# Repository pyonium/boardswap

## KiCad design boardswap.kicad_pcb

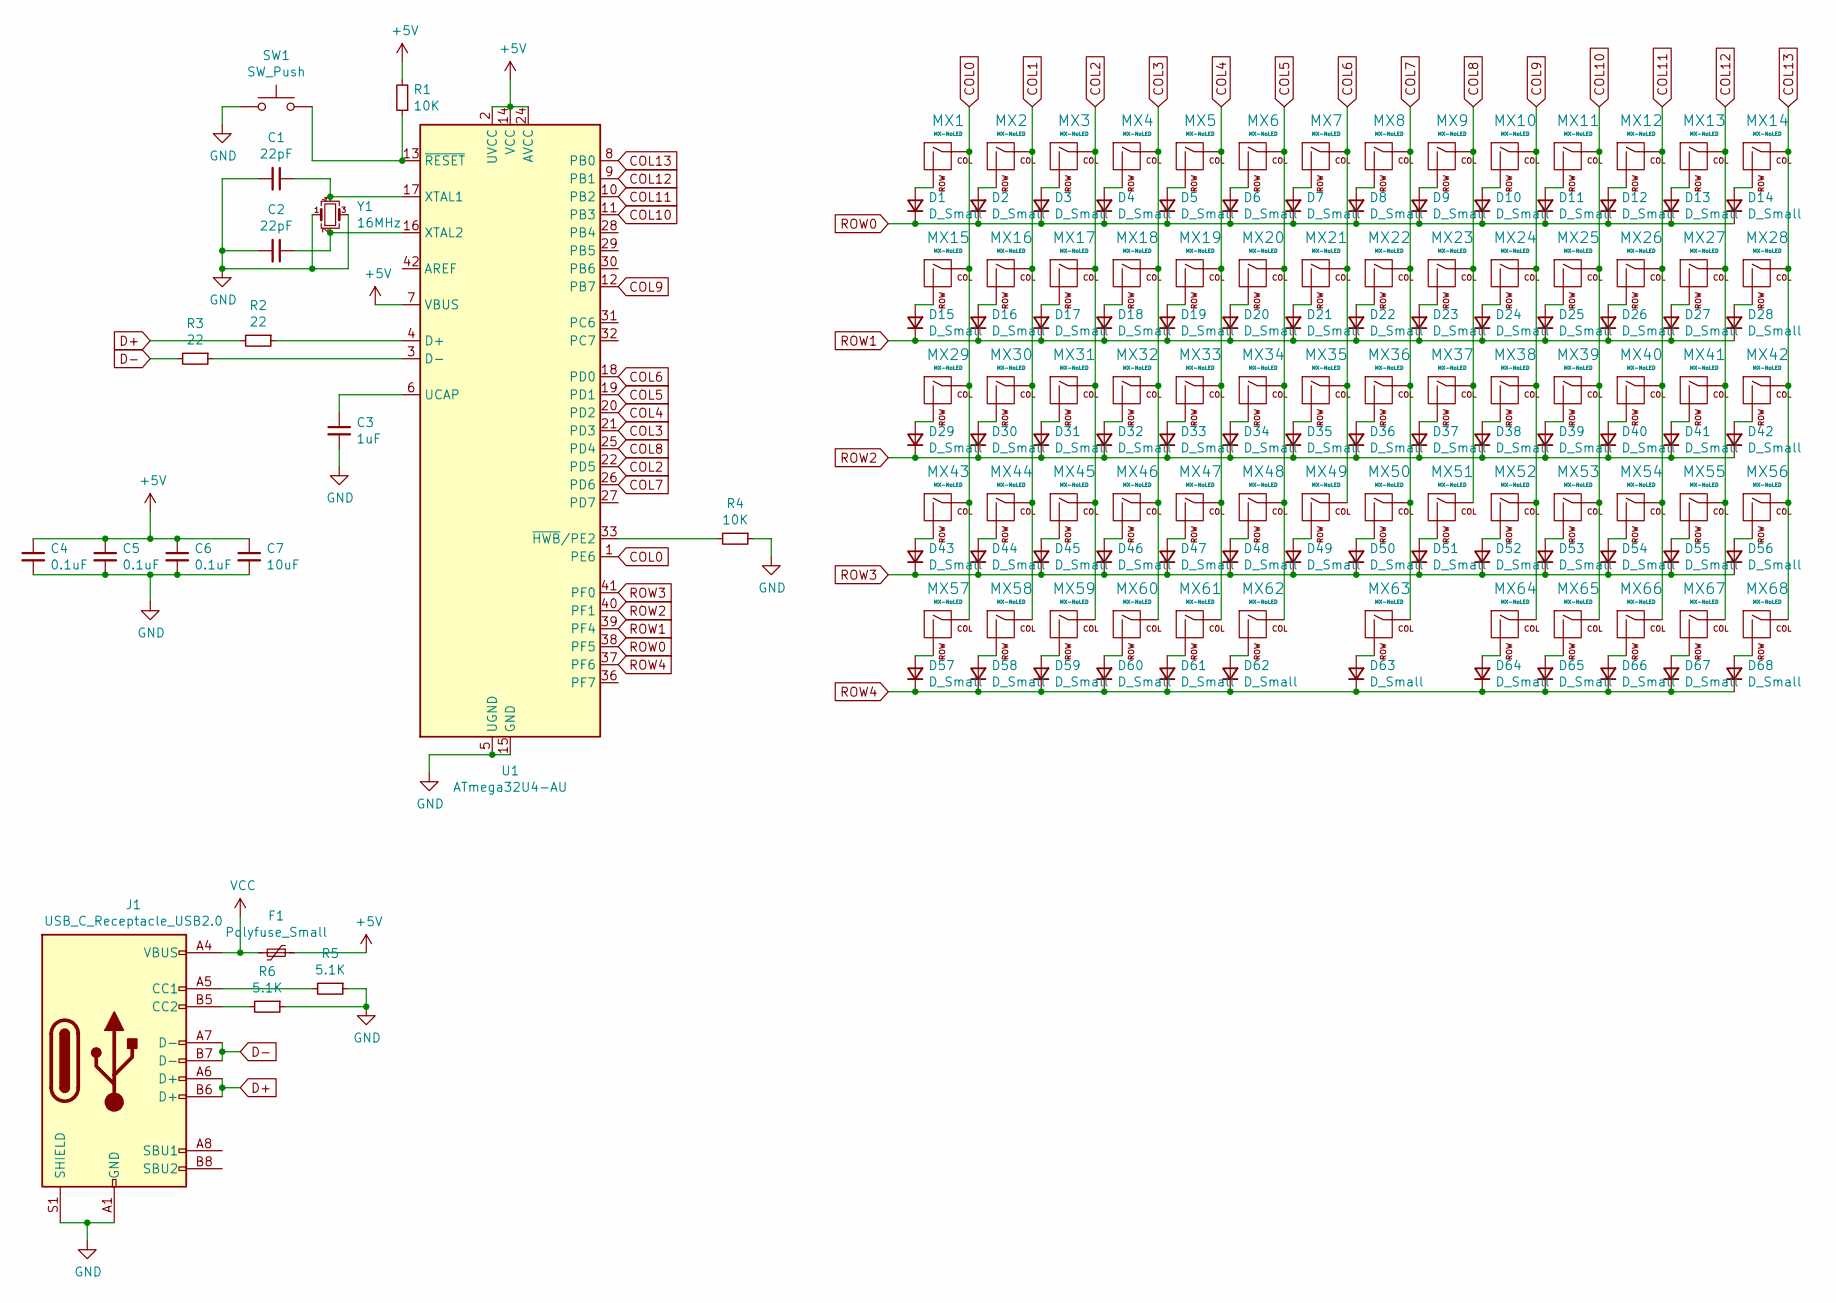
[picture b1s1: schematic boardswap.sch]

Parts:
C1, C2: 22pF; C_0805_2012Metric; LCSC C1804
C3: 1uF; C_0805_2012Metric; LCSC C282736
C4, C5, C6: 0.1uF; C_0603_1608Metric; LCSC C14663
C7: 10uF; C_0603_1608Metric; LCSC C344022
D1, D2, D3, D4, D5, D6, D7, D8, D9, D10, D11, D12, D13, D14, D15, D16, D17, D18, D19, D20, D21, D22, D23, D24, D25, D26, D27, D28, D29, D30, D31, D32, D33, D34, D35, D36, D37, D38, D39, D40, D41, D42, D43, D44, D45, D46, D47, D48, D49, D50, D51, D52, D53, D54, D55, D56, D57, D58, D59, D60, D61, D62, D63, D64, D65, D66, D67, D68: D_Small; D_SOD-123; LCSC C64885
F1: Polyfuse_Small; Fuse_1206_3216Metric; LCSC C70068
J1: USB_C_Receptacle_USB2.0; USB_C_Receptacle_HRO_TYPE-C-31-M-12
MX1, MX2, MX3, MX4, MX5, MX6, MX7, MX8, MX9, MX10, MX11, MX12, MX13, MX14, MX15, MX16, MX17, MX18, MX19, MX20, MX21, MX22, MX23, MX24, MX25, MX26, MX27, MX28, MX29, MX30, MX31, MX32, MX33, MX34, MX35, MX36, MX37, MX38, MX39, MX40, MX41, MX42, MX43, MX44, MX45, MX46, MX47, MX48, MX49, MX50, MX51, MX52, MX53, MX54, MX55, MX56, MX57, MX58, MX59, MX60, MX61, MX62, MX63, MX64, MX65, MX66, MX67, MX68: MX-NoLED; Kailh_socket_MX_alt
R1, R4: 10K; R_0805_2012Metric; LCSC C55866
R2, R3: 22; R_0805_2012Metric; LCSC C17561
R5, R6: 5.1K; R_0805_2012Metric; LCSC C64462
SW1: SW_Push; SW_SPST_SKQG_WithStem
U1: ATmega32U4-AU; TQFP-44_10x10mm_P0.8mm; LCSC C44854
Y1: 16MHz; Crystal_SMD_3225-4Pin_3.2x2.5mm; LCSC C13738

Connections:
+5V: C4.1, C5.1, C6.1, C7.1, F1.1, R1.2, U1.2 (UVCC), U1.7 (VBUS), U1.14 (VCC), U1.24 (AVCC), U1.34 (VCC), U1.44 (AVCC)
COL0: MX1.1 (COL), MX15.1 (COL), MX29.1 (COL), MX43.1 (COL), MX57.1 (COL), U1.1 (PE6)
COL1: MX2.1 (COL), MX16.1 (COL), MX30.1 (COL), MX44.1 (COL), MX58.1 (COL)
COL2: MX3.1 (COL), MX17.1 (COL), MX31.1 (COL), MX45.1 (COL), MX59.1 (COL), U1.22 (PD5)
COL3: MX4.1 (COL), MX18.1 (COL), MX32.1 (COL), MX46.1 (COL), MX60.1 (COL), U1.21 (PD3)
COL4: MX5.1 (COL), MX19.1 (COL), MX33.1 (COL), MX47.1 (COL), MX61.1 (COL), U1.20 (PD2)
COL5: MX6.1 (COL), MX20.1 (COL), MX34.1 (COL), MX48.1 (COL), MX62.1 (COL), U1.19 (PD1)
COL6: MX7.1 (COL), MX21.1 (COL), MX35.1 (COL), MX49.1 (COL), U1.18 (PD0)
COL7: MX8.1 (COL), MX22.1 (COL), MX36.1 (COL), MX50.1 (COL), MX63.1 (COL), U1.26 (PD6)
COL8: MX9.1 (COL), MX23.1 (COL), MX37.1 (COL), MX51.1 (COL), U1.25 (PD4)
COL9: MX10.1 (COL), MX24.1 (COL), MX38.1 (COL), MX52.1 (COL), MX64.1 (COL), U1.12 (PB7)
COL10: MX11.1 (COL), MX25.1 (COL), MX39.1 (COL), MX53.1 (COL), MX65.1 (COL), U1.11 (PB3)
COL11: MX12.1 (COL), MX26.1 (COL), MX40.1 (COL), MX54.1 (COL), MX66.1 (COL), U1.10 (PB2)
COL12: MX13.1 (COL), MX27.1 (COL), MX41.1 (COL), MX55.1 (COL), MX67.1 (COL), U1.9 (PB1)
COL13: MX14.1 (COL), MX28.1 (COL), MX42.1 (COL), MX56.1 (COL), MX68.1 (COL), U1.8 (PB0)
D+: J1.A6 (D+), J1.B6 (D+), R2.2
D-: J1.A7 (D-), J1.B7 (D-), R3.2
GND: C1.2, C2.2, C3.2, C4.2, C5.2, C6.2, C7.2, J1.A1 (GND), J1.A12 (GND), J1.B1 (GND), J1.B12 (GND), J1.S1 (SHIELD), R4.1, R5.1, R6.1, SW1.1, U1.5 (UGND), U1.15 (GND), U1.23 (GND), U1.35 (GND), U1.43 (GND), Y1.1, Y1.3
unnamed: C1.1, U1.17 (XTAL1), Y1.4
unnamed: C2.1, U1.16 (XTAL2), Y1.2
unnamed: C3.1, U1.6 (UCAP)
unnamed: D1.2 (A), MX1.2 (ROW)
unnamed: D2.2 (A), MX2.2 (ROW)
unnamed: D3.2 (A), MX3.2 (ROW)
unnamed: D4.2 (A), MX4.2 (ROW)
unnamed: D5.2 (A), MX5.2 (ROW)
unnamed: D6.2 (A), MX6.2 (ROW)
unnamed: D7.2 (A), MX7.2 (ROW)
unnamed: D8.2 (A), MX8.2 (ROW)
unnamed: D9.2 (A), MX9.2 (ROW)
unnamed: D10.2 (A), MX10.2 (ROW)
unnamed: D11.2 (A), MX11.2 (ROW)
unnamed: D12.2 (A), MX12.2 (ROW)
unnamed: D13.2 (A), MX13.2 (ROW)
unnamed: D14.2 (A), MX14.2 (ROW)
unnamed: D15.2 (A), MX15.2 (ROW)
unnamed: D16.2 (A), MX16.2 (ROW)
unnamed: D17.2 (A), MX17.2 (ROW)
unnamed: D18.2 (A), MX18.2 (ROW)
unnamed: D19.2 (A), MX19.2 (ROW)
unnamed: D20.2 (A), MX20.2 (ROW)
unnamed: D21.2 (A), MX21.2 (ROW)
unnamed: D22.2 (A), MX22.2 (ROW)
unnamed: D23.2 (A), MX23.2 (ROW)
unnamed: D24.2 (A), MX24.2 (ROW)
unnamed: D25.2 (A), MX25.2 (ROW)
unnamed: D26.2 (A), MX26.2 (ROW)
unnamed: D27.2 (A), MX27.2 (ROW)
unnamed: D28.2 (A), MX28.2 (ROW)
unnamed: D29.2 (A), MX29.2 (ROW)
unnamed: D30.2 (A), MX30.2 (ROW)
unnamed: D31.2 (A), MX31.2 (ROW)
unnamed: D32.2 (A), MX32.2 (ROW)
unnamed: D33.2 (A), MX33.2 (ROW)
unnamed: D34.2 (A), MX34.2 (ROW)
unnamed: D35.2 (A), MX35.2 (ROW)
unnamed: D36.2 (A), MX36.2 (ROW)
unnamed: D37.2 (A), MX37.2 (ROW)
unnamed: D38.2 (A), MX38.2 (ROW)
unnamed: D39.2 (A), MX39.2 (ROW)
unnamed: D40.2 (A), MX40.2 (ROW)
unnamed: D41.2 (A), MX41.2 (ROW)
unnamed: D42.2 (A), MX42.2 (ROW)
unnamed: D43.2 (A), MX43.2 (ROW)
unnamed: D44.2 (A), MX44.2 (ROW)
unnamed: D45.2 (A), MX45.2 (ROW)
unnamed: D46.2 (A), MX46.2 (ROW)
unnamed: D47.2 (A), MX47.2 (ROW)
unnamed: D48.2 (A), MX48.2 (ROW)
unnamed: D49.2 (A), MX49.2 (ROW)
unnamed: D50.2 (A), MX50.2 (ROW)
unnamed: D51.2 (A), MX51.2 (ROW)
unnamed: D52.2 (A), MX52.2 (ROW)
unnamed: D53.2 (A), MX53.2 (ROW)
unnamed: D54.2 (A), MX54.2 (ROW)
unnamed: D55.2 (A), MX55.2 (ROW)
unnamed: D56.2 (A), MX56.2 (ROW)
unnamed: D57.2 (A), MX57.2 (ROW)
unnamed: D58.2 (A), MX58.2 (ROW)
unnamed: D59.2 (A), MX59.2 (ROW)
unnamed: D60.2 (A), MX60.2 (ROW)
unnamed: D61.2 (A), MX61.2 (ROW)
unnamed: D62.2 (A), MX62.2 (ROW)
unnamed: D63.2 (A), MX63.2 (ROW)
unnamed: D64.2 (A), MX64.2 (ROW)
unnamed: D65.2 (A), MX65.2 (ROW)
unnamed: D66.2 (A), MX66.2 (ROW)
unnamed: D67.2 (A), MX67.2 (ROW)
unnamed: D68.2 (A), MX68.2 (ROW)
unnamed: J1.A5 (CC1), R5.2
unnamed: J1.B5 (CC2), R6.2
unnamed: R1.1, SW1.2, U1.13 (~RESET)
unnamed: R2.1, U1.4 (D+)
unnamed: R3.1, U1.3 (D-)
unnamed: R4.2, U1.33 (~HWB~/PE2)
ROW0: D1.1 (K), D2.1 (K), D3.1 (K), D4.1 (K), D5.1 (K), D6.1 (K), D7.1 (K), D8.1 (K), D9.1 (K), D10.1 (K), D11.1 (K), D12.1 (K), D13.1 (K), D14.1 (K), U1.38 (PF5)
ROW1: D15.1 (K), D16.1 (K), D17.1 (K), D18.1 (K), D19.1 (K), D20.1 (K), D21.1 (K), D22.1 (K), D23.1 (K), D24.1 (K), D25.1 (K), D26.1 (K), D27.1 (K), D28.1 (K), U1.39 (PF4)
ROW2: D29.1 (K), D30.1 (K), D31.1 (K), D32.1 (K), D33.1 (K), D34.1 (K), D35.1 (K), D36.1 (K), D37.1 (K), D38.1 (K), D39.1 (K), D40.1 (K), D41.1 (K), D42.1 (K), U1.40 (PF1)
ROW3: D43.1 (K), D44.1 (K), D45.1 (K), D46.1 (K), D47.1 (K), D48.1 (K), D49.1 (K), D50.1 (K), D51.1 (K), D52.1 (K), D53.1 (K), D54.1 (K), D55.1 (K), D56.1 (K), U1.41 (PF0)
ROW4: D57.1 (K), D58.1 (K), D59.1 (K), D60.1 (K), D61.1 (K), D62.1 (K), D63.1 (K), D64.1 (K), D65.1 (K), D66.1 (K), D67.1 (K), D68.1 (K), U1.37 (PF6)
VCC: F1.2, J1.A4 (VBUS), J1.A9 (VBUS), J1.B4 (VBUS), J1.B9 (VBUS)

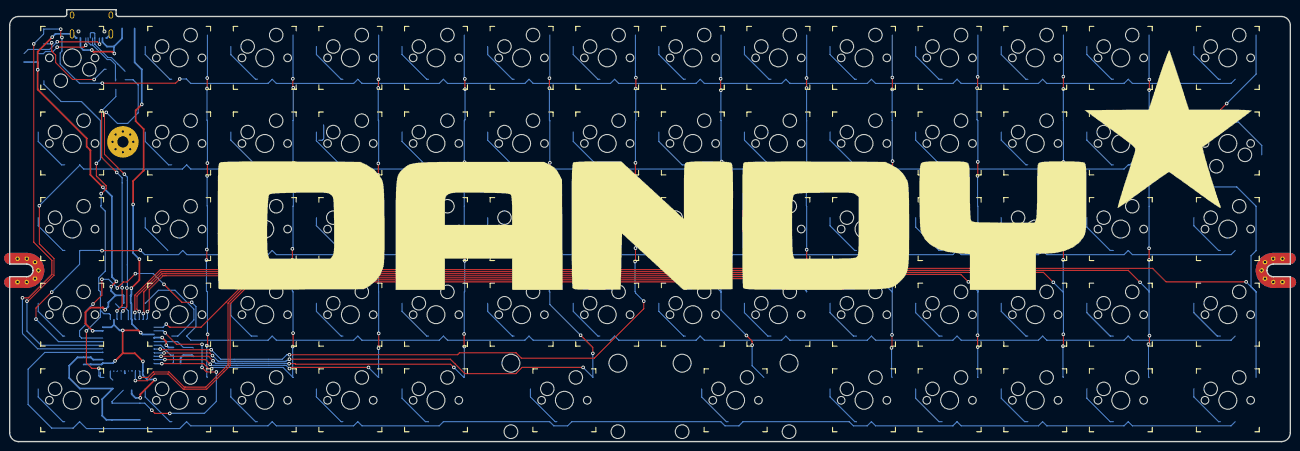
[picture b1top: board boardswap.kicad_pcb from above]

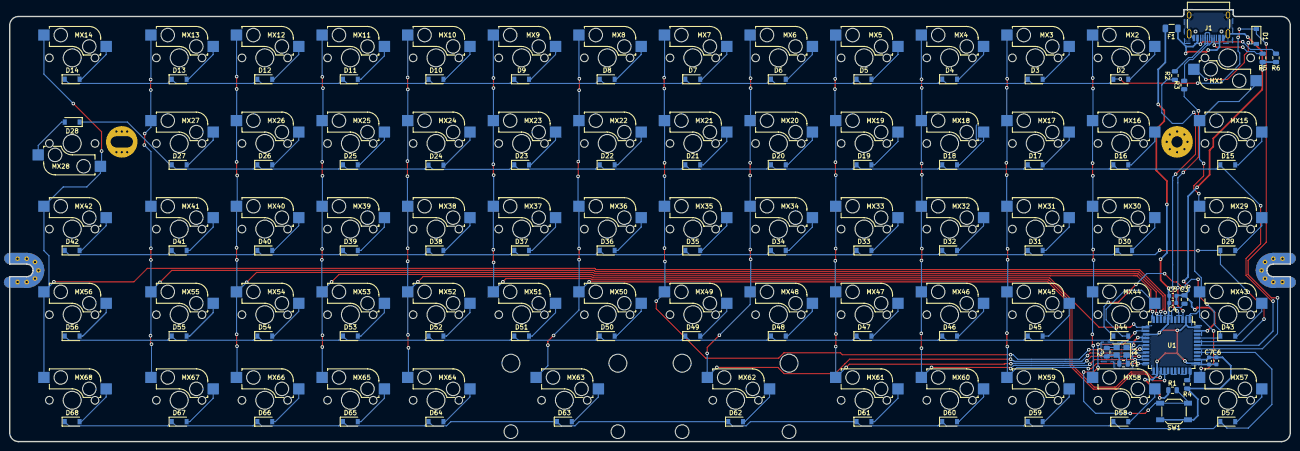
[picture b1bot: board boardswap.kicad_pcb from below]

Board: 2 copper layers, 285.0 x 96.1 mm, 155 parts (86 on the bottom side), 101 nets.

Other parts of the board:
OUTLINE: 60_Outline; 60_Outline-Modded

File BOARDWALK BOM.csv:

Comment,Designator,Footprint,LCSC
"22pF","C1,C2","Capacitor_SMD:C_0805_2012Metric","C1804"
"1uF","C3","Capacitor_SMD:C_0805_2012Metric","C28323"
"0.1uF","C4,C5,C6","Capacitor_SMD:C_0603_1608Metric","C14663"
"10uF","C7","Capacitor_SMD:C_0603_1608Metric","C19702"
"D_Small","D1,D2,D3,D4,D5,D6,D7,D8,D9,D10,D11,D12,D13,D14,D15,D16,D17,D18,D19,D20,D21,D22,D23,D24,D25,D26,D27,D28,D29,D30,D31,D32,D33,D34,D35,D36,D37,D38,D39,D40,D41,D42,D43,D44,D45,D46,D47,D48,D49,D50,D51,D52,D53,D54,D55,D56,D57,D58,D59,D60,D61,D62,D63,D64,D65,D66,D67,D68","Diode_SMD:D_SOD-123","C81598"
"Polyfuse_Small","F1","Fuse:Fuse_1206_3216Metric","C70068"
"ICSP","ICSP1","Connector_PinHeader_2.54mm:PinHeader_2x03_P2.54mm_Vertical",""
"USB_C_Receptacle_USB2.0","J1","Connector_USB:USB_C_Receptacle_HRO_TYPE-C-31-M-12",""
"MX-NoLED","MX1,MX2,MX3,MX4,MX5,MX6,MX7,MX8,MX9,MX10,MX11,MX12,MX13,MX14,MX15,MX16,MX17,MX18,MX19,MX20,MX21,MX22,MX23,MX24,MX25,MX26,MX27,MX28,MX29,MX30,MX31,MX32,MX33,MX34,MX35,MX36,MX37,MX38,MX39,MX40,MX41,MX42,MX43,MX44,MX45,MX46,MX47,MX48,MX49,MX50,MX51,MX52,MX53,MX54,MX55,MX56,MX57,MX58,MX59,MX60,MX61,MX62,MX63,MX64,MX65,MX66,MX67,MX68","switchprint:Kailh_socket_MX_alt",""
"22","R2,R3","Resistor_SMD:R_0805_2012Metric","C17561"
"10K","R1,R4","Resistor_SMD:R_0805_2012Metric","C17414"
"5.1K","R5,R6","Resistor_SMD:R_0805_2012Metric","C27834"
"SW_Push","SW1","Button_Switch_SMD:SW_SPST_SKQG_WithStem",""
"ATmega32U4-AU","U1","Package_QFP:TQFP-44_10x10mm_P0.8mm","C44854"
"16MHz","Y1","Crystal:Crystal_SMD_3225-4Pin_3.2x2.5mm","C13738"

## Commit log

2020-08-10 added libs
2020-08-10 started schematic
2020-08-10 in the middle of routing commit
2020-08-10 did most placement
2020-08-10 hewwo backups owo
2020-08-10 fixed traces
2020-08-11 added stabs
2020-08-11 placed components
2020-08-11 routed everything except matrix to mcu
2020-08-11 done routing probably
2020-08-11 added fill
2020-08-12 rotated mcu, begrudgingly
2020-08-12 fixed resistor values
2020-08-12 fixed silkscreen
2020-08-12 fixed silkscreen thing
2020-08-12 fixed footprint
2020-08-12 removed unnecessary files
2020-08-12 fixed unnecessary reference
2020-08-12 added more stuff
2020-08-12 made everything nice
2020-08-12 prettified logo
2020-08-12 pretty logo
2020-08-29 redid a lot
